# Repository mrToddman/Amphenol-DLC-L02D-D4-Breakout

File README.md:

# Amphenol DLC-L02D-D4 Breakout

<br/>

This is a breakout board and Arduino sketch for testing Amphenol DLC-L02D-D4 differential pressure sensor

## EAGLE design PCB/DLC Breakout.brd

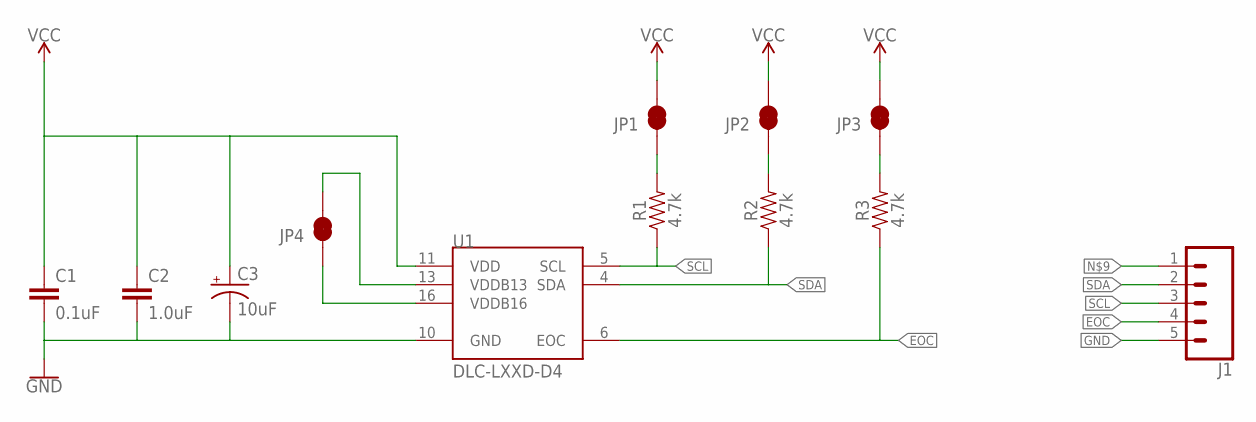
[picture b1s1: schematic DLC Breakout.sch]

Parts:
C1: 0.1uF; 0603
C2: 1.0uF; 0603
C3: 10uF; EIA3216
J1: CONN_05; 1X05
JP1, JP2, JP3, JP4: JUMPER-SMT_2_NC_TRACE_NO-SILK; SMT-JUMPER_2_NC_TRACE_NO-SILK
R1, R2, R3: 4.7k; 0603
U1: DLC-LXXD-D4

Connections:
EOC: J1.4, R3.1, U1.6 (EOC)
GND: C1.2, C2.2, C3.-, J1.5, U1.10 (GND)
unnamed: JP1.2, R1.2
unnamed: JP2.2, R2.2
unnamed: JP3.2, R3.2
unnamed: C1.1, C2.1, C3.+, J1.1, JP1.1, JP2.1, JP3.1, U1.11 (VDD)
unnamed: JP4.2, U1.16 (VDDB16)
SCL: J1.3, R1.1, U1.5 (SCL)
SDA: J1.2, R2.1, U1.4 (SDA)
VDDB: JP4.1, U1.13 (VDDB13)

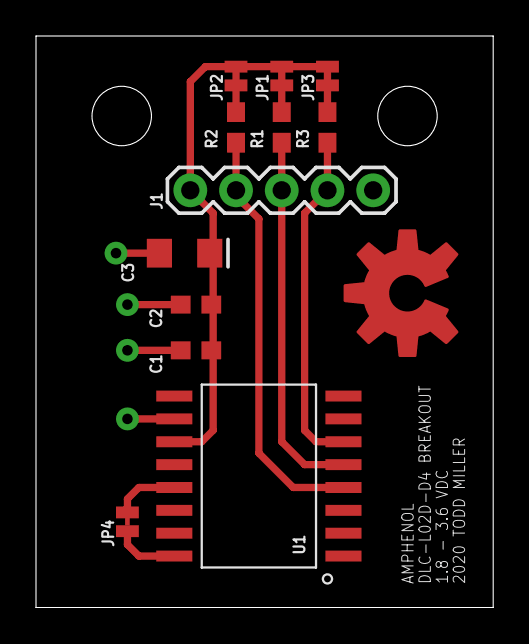
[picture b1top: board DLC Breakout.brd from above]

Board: 2 copper layers, 25.4 x 31.8 mm, 15 parts (0 on the bottom side), 10 nets.

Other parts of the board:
U$1, U$2: STAND-OFF
U$3: OSHW-LOGO-L_COPPER

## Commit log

2023-01-11 readme
2023-01-13 found this in old project folder
    used to generate theoretical pressure-velocity values for pitot tube sensor design

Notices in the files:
parts and their libraries:
SparkFun-Capacitors: Licensing: Creative Commons ShareAlike 4.0 International - https://creativecommons.org/licenses/by-sa/4.0
